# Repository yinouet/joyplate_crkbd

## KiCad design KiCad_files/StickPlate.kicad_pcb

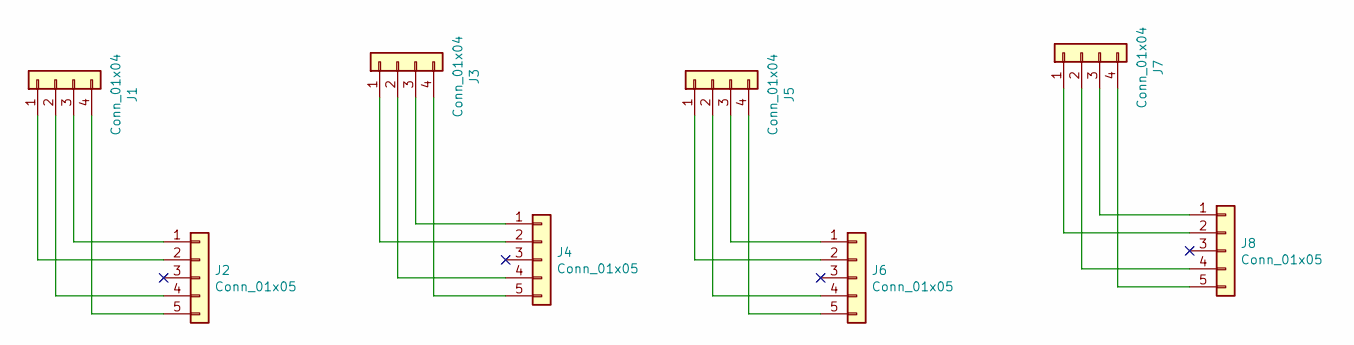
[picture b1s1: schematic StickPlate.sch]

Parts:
J1, J3, J5, J7: Conn_01x04; PAD_4P
J2, J4, J6, J8: Conn_01x05; uxcell_FFC_Connector_1x5_P0

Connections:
unnamed: J1.1, J2.2
unnamed: J1.2, J2.4
unnamed: J1.3, J2.1
unnamed: J1.4, J2.5
unnamed: J3.1, J4.2
unnamed: J3.2, J4.4
unnamed: J3.3, J4.1
unnamed: J3.4, J4.5
unnamed: J5.1, J6.2
unnamed: J5.2, J6.4
unnamed: J5.3, J6.1
unnamed: J5.4, J6.5
unnamed: J7.1, J8.2
unnamed: J7.2, J8.4
unnamed: J7.3, J8.1
unnamed: J7.4, J8.5

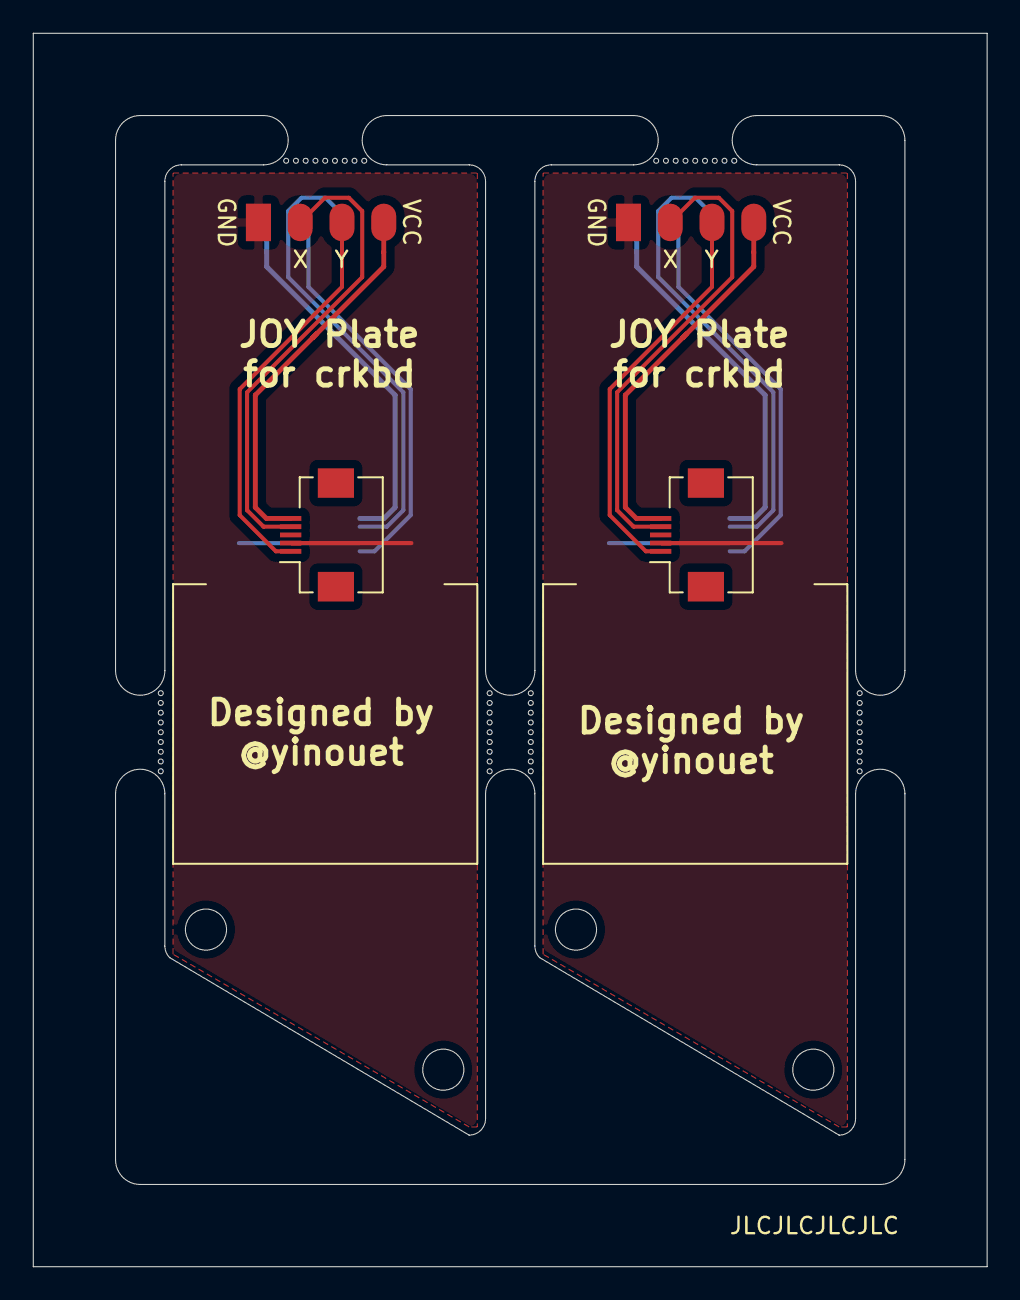
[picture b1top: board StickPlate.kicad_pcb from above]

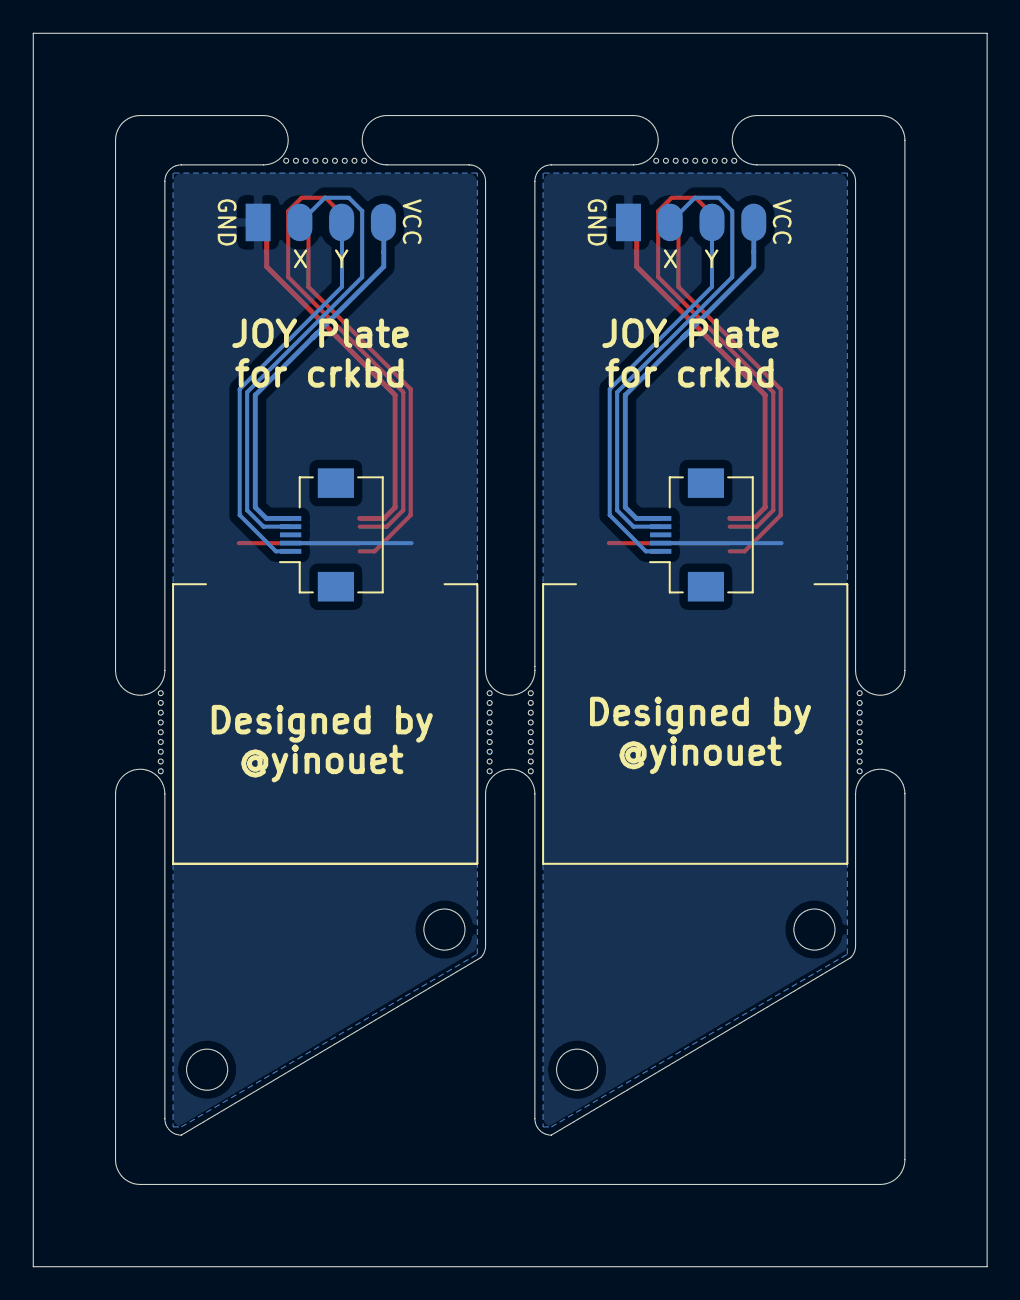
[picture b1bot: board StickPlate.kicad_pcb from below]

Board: 2 copper layers, 58.0 x 75.0 mm, 8 parts (4 on the bottom side), 16 nets.

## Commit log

2021-10-20 Uploaded
